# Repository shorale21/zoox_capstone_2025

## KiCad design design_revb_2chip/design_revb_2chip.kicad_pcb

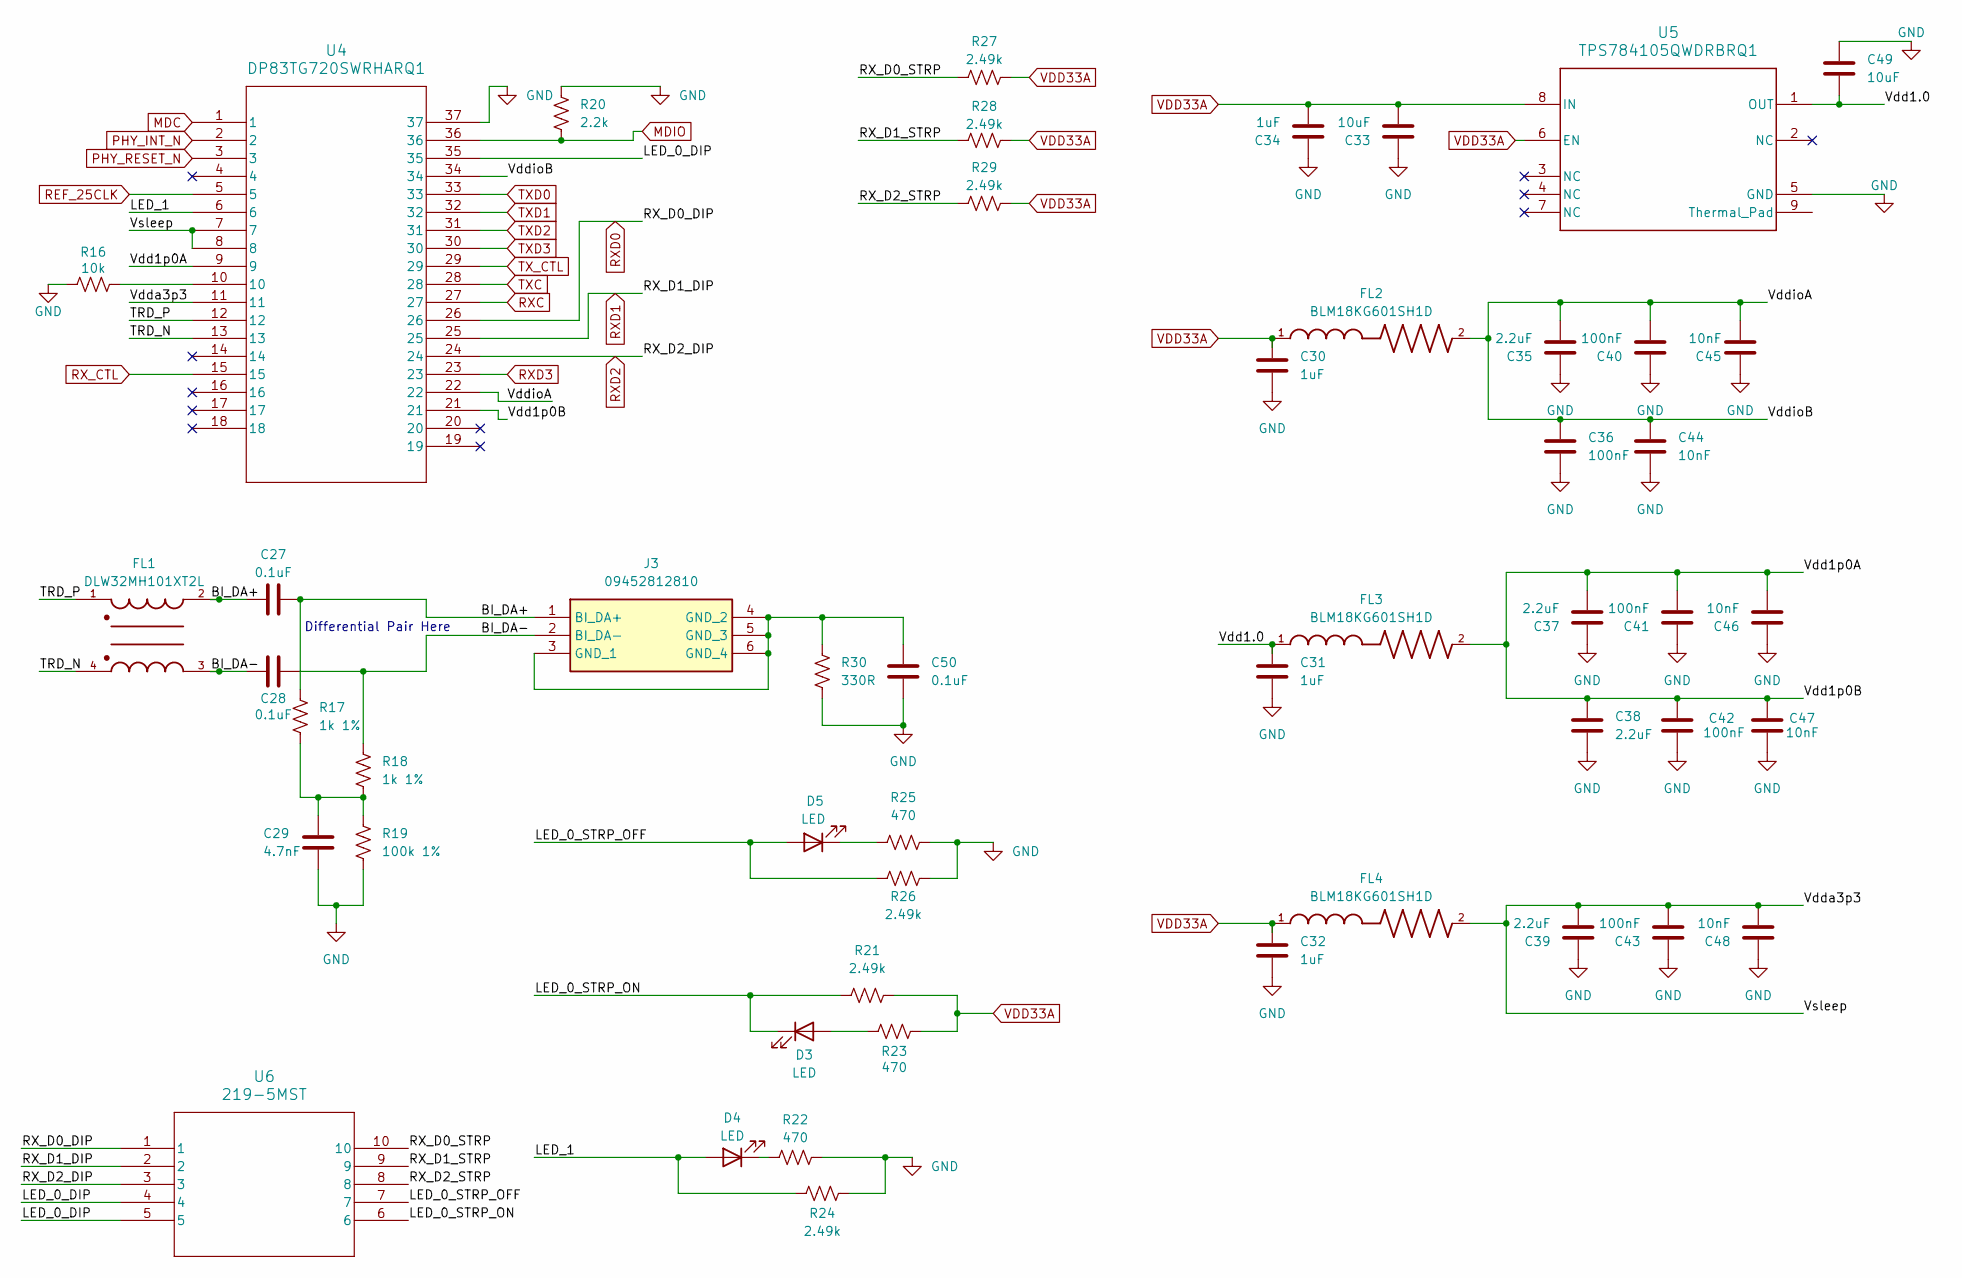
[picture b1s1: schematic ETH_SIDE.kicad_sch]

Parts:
C27, C28, C50: 0.1uF; C_0402_1005Metric
C29: 4.7nF; C_0603_1608Metric
C30, C32, C34: 1uF; C_0603_1608Metric
C31: 1uF; C_0402_1005Metric
C33: 10uF; C_0603_1608Metric
C35, C37, C38, C39: 2.2uF; C_0402_1005Metric
C36, C40, C41, C42, C43: 100nF; C_0402_1005Metric
C44, C46, C47, C48: 10nF; C_0402_1005Metric
C45: 10nF; C_0603_1608Metric
C49: 10uF; C_0402_1005Metric
D3, D4, D5: LED; LED_0603_1608Metric
FL1: DLW32MH101XT2L; FIL_DLW32MH101XT2L; PARTREV N/A
FL2, FL3, FL4: BLM18KG601SH1D; BEADC1608X95N
J3: 09452812810; hartingt1; Manufacturer_Part_Number 09452812810; Mouser Part Number 617-09452812810
R16: 10k; R_0805_2012Metric
R17, R18: 1k 1%; R_0805_2012Metric
R19: 100k 1%; R_0805_2012Metric
R20: 2.2k; R_0805_2012Metric
R21, R24, R26, R27, R28, R29: 2.49k; R_0805_2012Metric
R22, R23, R25: 470; R_0805_2012Metric
R30: 330R; R_0805_2012Metric
U4: DP83TG720SWRHARQ1; VQFN36_6X6_TEX
U5: TPS784105QWDRBRQ1; DRB0008J-IPC_A
U6: 219-5MST; SW5_219SMT

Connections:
/ETH_SIDE/BI_DA+: C27.1, C27.2, FL1.2, J3.1 (BI_DA+), R17.1
/ETH_SIDE/BI_DA-: C28.1, C28.2, FL1.3, J3.2 (BI_DA-), R18.1
/ETH_SIDE/LED_0_DIP: U4.35, U6.4, U6.5
/ETH_SIDE/LED_0_STRP_OFF: D5.2 (A), R26.1, U6.7
/ETH_SIDE/LED_0_STRP_ON: D3.1 (K), R21.1, U6.6
/ETH_SIDE/LED_1: D4.2 (A), R24.1, U4.6
/ETH_SIDE/RX_D0_STRP: R27.2, U6.10
/ETH_SIDE/RX_D1_STRP: R28.2, U6.9
/ETH_SIDE/RX_D2_STRP: R29.2, U6.8
/ETH_SIDE/TRD_N: FL1.4, U4.13
/ETH_SIDE/TRD_P: FL1.1, U4.12
/ETH_SIDE/Vdd1.0: C31.1, C49.2, FL3.1, U5.1 (OUT)
/ETH_SIDE/Vdd1p0A: C37.2, C38.1, C41.2, C42.1, C46.2, C47.1, FL3.2, U4.9, U4.21
/ETH_SIDE/Vdda3p3: C39.2, C43.2, C48.2, FL4.2, U4.7, U4.8, U4.11
/ETH_SIDE/VddioA: C35.2, C36.1, C40.2, C44.1, C45.2, FL2.2, U4.22, U4.34; also elsewhere on the board
GND: C29.2, C30.2, C31.2, C32.2, C33.1, C34.1, C35.1, C36.2, C37.1, C38.2, C39.1, C40.1, C41.1, C42.2, C43.1, C44.2, C45.1, C46.1, C47.2, C48.1, C49.1, C50.2, R16.2, R19.2, R20.1, R22.1, R24.2, R25.1, R26.2, R30.1, U4.37, U5.5 (GND); also elsewhere on the board
MDC: U4.1; also elsewhere on the board
MDIO: R20.2, U4.36; also elsewhere on the board
unnamed: C29.1, R17.2, R18.2, R19.1
unnamed: D3.2 (A), R23.1
unnamed: D4.1 (K), R22.2
unnamed: D5.1 (K), R25.2
unnamed: C50.1, J3.3 (GND_1), J3.4 (GND_2), J3.5 (GND_3), J3.6 (GND_4), R30.2
unnamed: R16.1, U4.10
PHY_INT_N: U4.2; also elsewhere on the board
PHY_RESET_N: U4.3; also elsewhere on the board
REF_25CLK: U4.5; also elsewhere on the board
RXC: U4.27; also elsewhere on the board
RXD0: U4.26, U6.1; also elsewhere on the board
RXD1: U4.25, U6.2; also elsewhere on the board
RXD2: U4.24, U6.3; also elsewhere on the board
RXD3: U4.23; also elsewhere on the board
RX_CTL: U4.15; also elsewhere on the board
TXC: U4.28; also elsewhere on the board
TXD0: U4.33; also elsewhere on the board
TXD1: U4.32; also elsewhere on the board
TXD2: U4.31; also elsewhere on the board
TXD3: U4.30; also elsewhere on the board
TX_CTL: U4.29; also elsewhere on the board
VDD33A: C30.1, C32.1, C33.2, C34.2, FL2.1, FL4.1, R21.2, R23.2, R27.1, R28.1, R29.1, U5.6 (EN), U5.8 (IN); also elsewhere on the board

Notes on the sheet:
Differential Pair Here

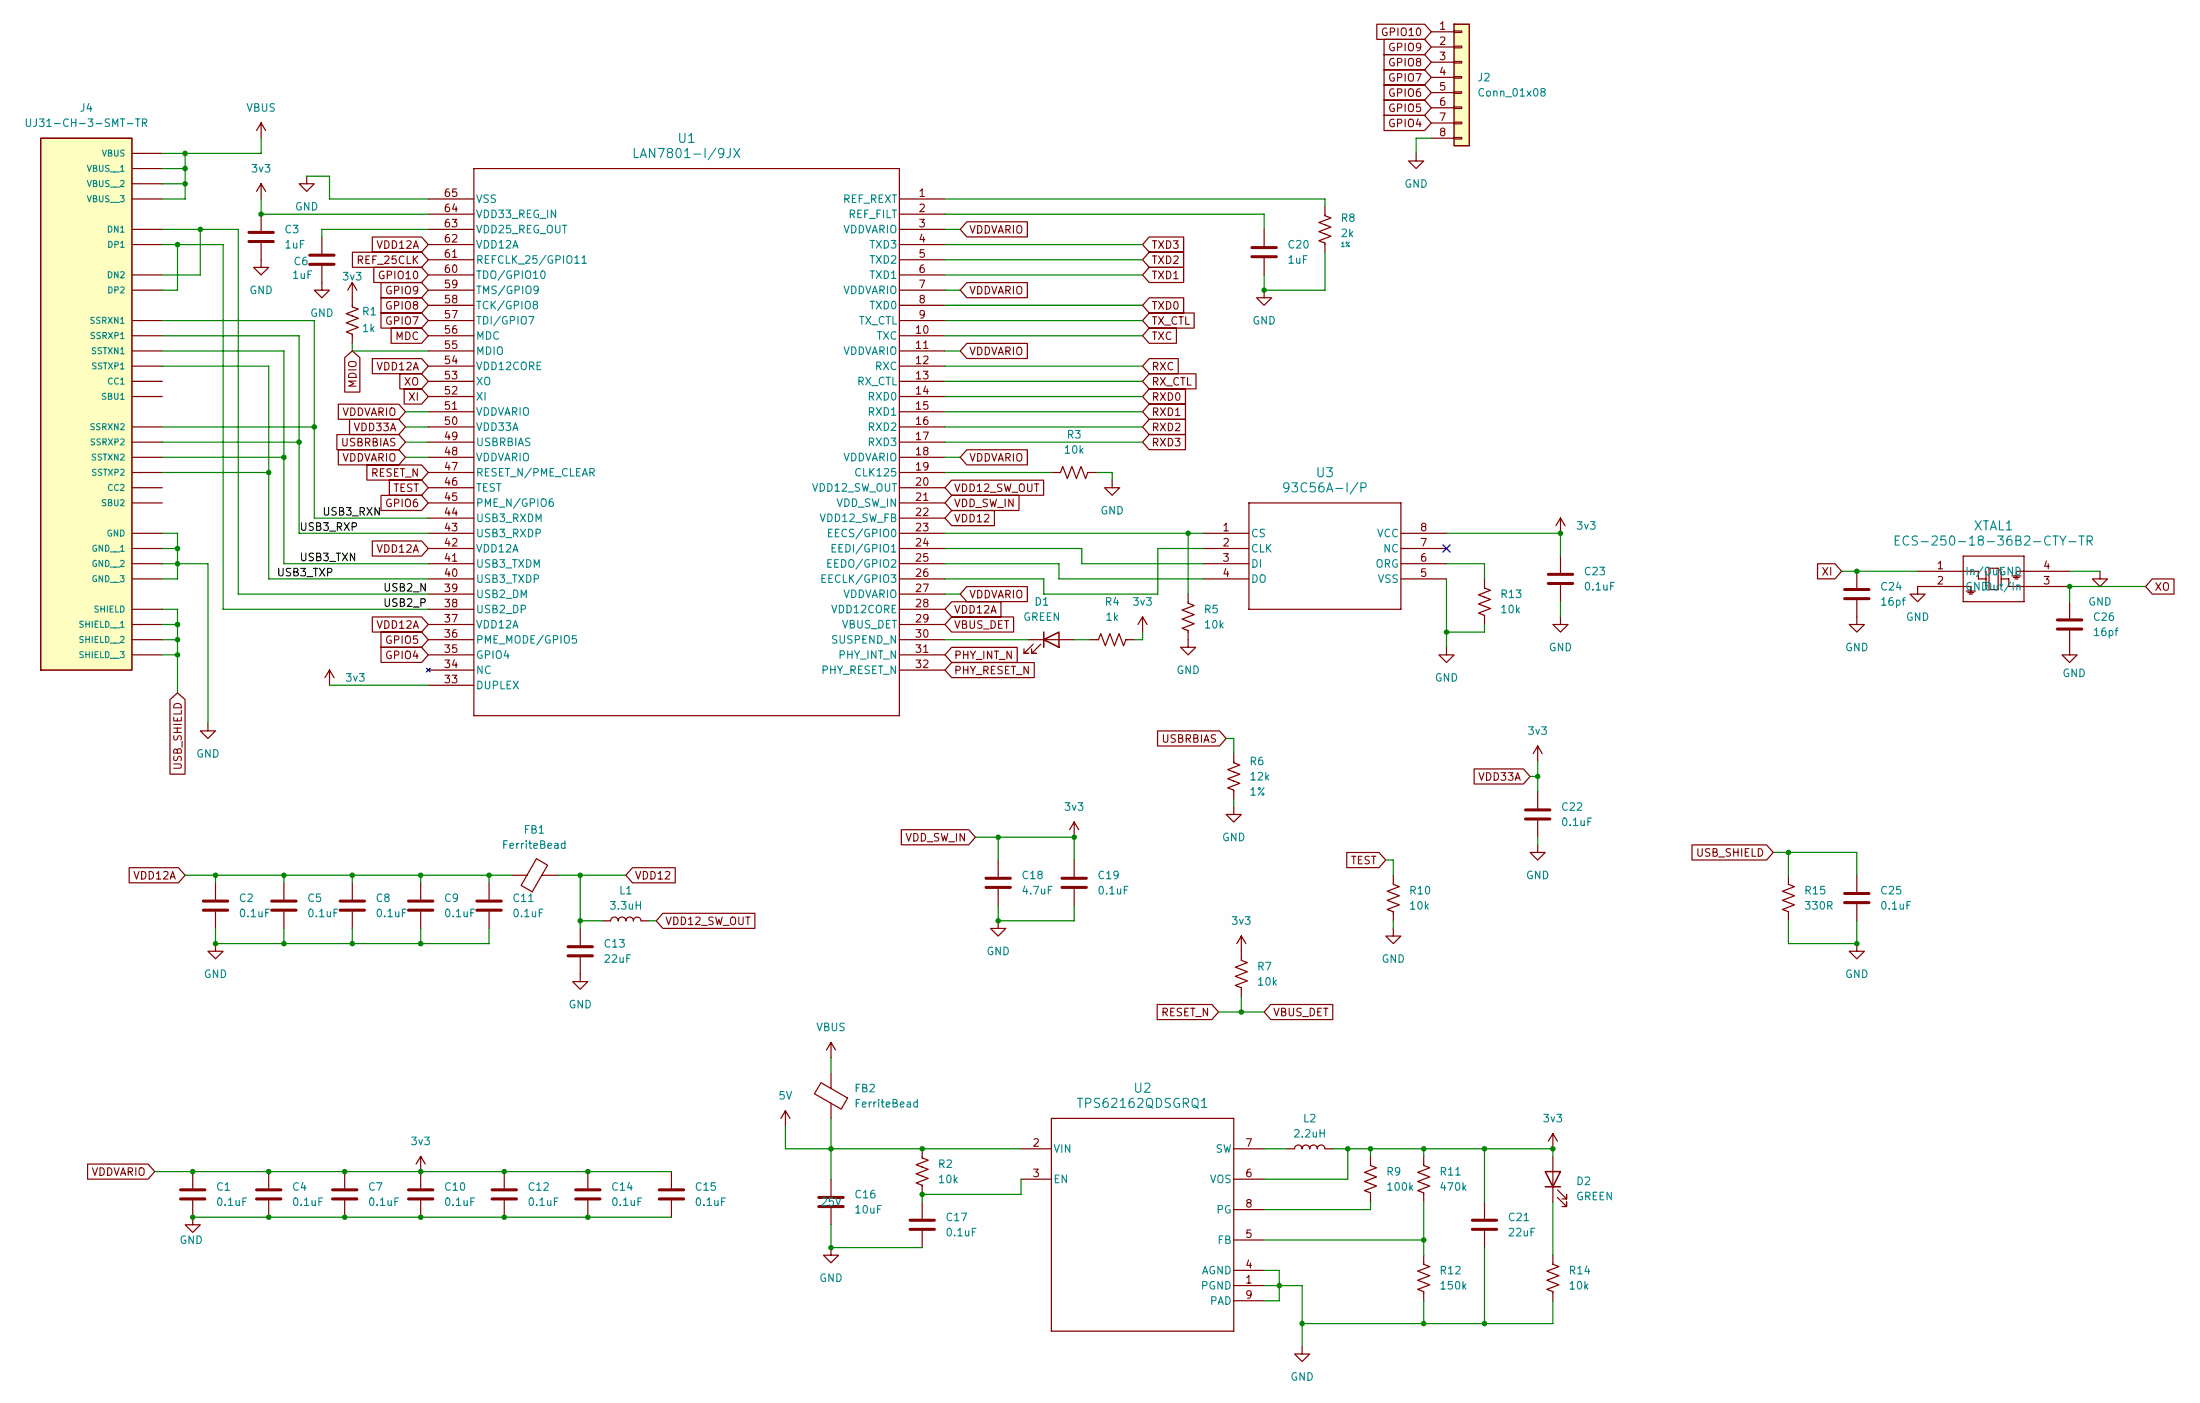
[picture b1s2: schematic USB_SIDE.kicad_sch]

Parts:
C1, C2, C4, C5, C7, C8, C9, C10, C11, C12, C14, C15, C17, C19, C22, C23, C25: 0.1uF; C_0402_1005Metric
C3: 1uF; C_0603_1608Metric
C6, C20: 1uF; C_0402_1005Metric
C13, C21: 22uF; C_0603_1608Metric
C16: 10uF; C_0603_1608Metric; voltage 25V
C18: 4.7uF; C_0603_1608Metric
C24, C26: 16pf; C_0402_1005Metric
D1, D2: GREEN; LED_0603_1608Metric
FB1, FB2: FerriteBead; BEADC1608X95N
J2: Conn_01x08; PinHeader_1x08_P2.00mm_Horizontal
J4: UJ31-CH-3-SMT-TR; CUI_UJ31-CH-3-SMT-TR
L1: 3.3uH; L_Wurth_WE-LQSH-3012
L2: 2.2uH; L_1008_2520Metric
R1, R4: 1k; R_0805_2012Metric
R2, R3, R5, R7, R10, R13, R14: 10k; R_0805_2012Metric
R6: 12k; R_0402_1005Metric; tolerance 1%
R8: 2k; R_0402_1005Metric; tolerance 1%
R9: 100k; R_0805_2012Metric
R11: 470k; R_0805_2012Metric
R12: 150k; R_0805_2012Metric
R15: 330R; R_0805_2012Metric
U1: LAN7801-I/9JX; SQFN64_9JX_MCH
U2: TPS62162QDSGRQ1; DSG0008A
U3: 93C56A-I/P; PDIP8_300MC_MCH
XTAL1: ECS-250-18-36B2-CTY-TR; ECX-2236B2_ECS

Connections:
5V: C16.1, FB2.1, R2.2, U2.2 (VIN)
/USB_SIDE/USB2_N: J4.A7 (DN1), J4.B7 (DN2), U1.39 (USB2_DM)
/USB_SIDE/USB2_P: J4.A6 (DP1), J4.B6 (DP2), U1.38 (USB2_DP)
/USB_SIDE/USB3_RXN: J4.A10 (SSRXN2), J4.B10 (SSRXN1), U1.44 (USB3_RXDM)
/USB_SIDE/USB3_RXP: J4.A11 (SSRXP2), J4.B11 (SSRXP1), U1.43 (USB3_RXDP)
/USB_SIDE/USB3_TXN: J4.A3 (SSTXN1), J4.B3 (SSTXN2), U1.41 (USB3_TXDM)
/USB_SIDE/USB3_TXP: J4.A2 (SSTXP1), J4.B2 (SSTXP2), U1.40 (USB3_TXDP)
GND: C1.2, C2.2, C3.2, C4.2, C5.2, C6.2, C7.2, C8.2, C9.2, C10.2, C11.2, C12.2, C13.2, C14.2, C15.2, C16.2, C17.2, C18.2, C19.2, C20.2, C21.2, C22.2, C23.2, C24.2, C25.2, C26.2, J2.8, J4.A1 (GND), J4.A12 (GND__1), J4.B1 (GND__2), J4.B12 (GND__3), R3.1, R5.1, R6.1, R8.1, R10.1, R12.1, R13.1, R14.1, R15.1, U1.65 (VSS), U2.1 (PGND), U2.4 (AGND), U2.9 (PAD), U2.V, U3.5 (VSS), XTAL1.2 (GND), XTAL1.4 (GND); also elsewhere on the board
GPIO4: J2.7, U1.35 (GPIO4)
GPIO5: J2.6, U1.36 (PME_MODE/GPIO5)
GPIO6: J2.5, U1.45 (PME_N/GPIO6)
GPIO7: J2.4, U1.57 (TDI/GPIO7)
GPIO8: J2.3, U1.58 (TCK/GPIO8)
GPIO9: J2.2, U1.59 (TMS/GPIO9)
GPIO10: J2.1, U1.60 (TDO/GPIO10)
MDC: U1.56 (MDC); also elsewhere on the board
MDIO: R1.1, U1.55 (MDIO); also elsewhere on the board
unnamed: D1.2 (A), R4.2
unnamed: D1.1 (K), U1.30 (SUSPEND_N)
unnamed: D2.1 (K), R14.2
unnamed: R3.2, U1.19 (CLK125)
unnamed: U1.26 (EECLK/GPIO3), U3.2 (CLK)
unnamed: R5.2, U1.23 (EECS/GPIO0), U3.1 (CS)
unnamed: U1.24 (EEDI/GPIO1), U3.3 (DI)
unnamed: U1.25 (EEDO/GPIO2), U3.4 (DO)
unnamed: C20.1, U1.2 (REF_FILT)
unnamed: R8.2, U1.1 (REF_REXT)
unnamed: C6.1, U1.63 (VDD25_REG_OUT)
unnamed: C17.1, R2.1, U2.3 (EN)
unnamed: R11.1, R12.2, U2.5 (FB)
unnamed: R9.1, U2.8 (PG)
unnamed: L2.1, U2.7 (SW)
unnamed: R13.2, U3.6 (ORG)
PHY_INT_N: U1.31 (PHY_INT_N); also elsewhere on the board
PHY_RESET_N: U1.32 (PHY_RESET_N); also elsewhere on the board
REF_25CLK: U1.61 (REFCLK_25/GPIO11); also elsewhere on the board
RESET_N: R7.1, U1.29 (VBUS_DET), U1.47 (RESET_N/PME_CLEAR)
RXC: U1.12 (RXC); also elsewhere on the board
RXD0: U1.14 (RXD0); also elsewhere on the board
RXD1: U1.15 (RXD1); also elsewhere on the board
RXD2: U1.16 (RXD2); also elsewhere on the board
RXD3: U1.17 (RXD3); also elsewhere on the board
RX_CTL: U1.13 (RX_CTL); also elsewhere on the board
TEST: R10.2, U1.46 (TEST)
TXC: U1.10 (TXC); also elsewhere on the board
TXD0: U1.8 (TXD0); also elsewhere on the board
TXD1: U1.6 (TXD1); also elsewhere on the board
TXD2: U1.5 (TXD2); also elsewhere on the board
TXD3: U1.4 (TXD3); also elsewhere on the board
TX_CTL: U1.9 (TX_CTL); also elsewhere on the board
USBRBIAS: R6.2, U1.49 (USBRBIAS)
USB_SHIELD: C25.1, J4.SH1 (SHIELD), J4.SH2 (SHIELD__1), J4.SH3 (SHIELD__2), J4.SH4 (SHIELD__3), R15.2
VBUS: FB2.2, J4.A4 (VBUS), J4.A9 (VBUS__1), J4.B4 (VBUS__2), J4.B9 (VBUS__3)
VDD12: C13.1, FB1.2, L1.1, U1.22 (VDD12_SW_FB)
VDD12A: C2.1, C5.1, C8.1, C9.1, C11.1, FB1.1, U1.28 (VDD12CORE), U1.37 (VDD12A), U1.42 (VDD12A), U1.54 (VDD12CORE), U1.62 (VDD12A)
VDD12_SW_OUT: L1.2, U1.20 (VDD12_SW_OUT)
VDD33A: C1.1, C3.1, C4.1, C7.1, C10.1, C12.1, C14.1, C15.1, C18.1, C19.1, C21.1, C22.1, C23.1, D2.2 (A), L2.2, R1.2, R4.1, R7.2, R9.2, R11.2, U1.3 (VDDVARIO), U1.7 (VDDVARIO), U1.11 (VDDVARIO), U1.18 (VDDVARIO), U1.21 (VDD_SW_IN), U1.27 (VDDVARIO), U1.33 (DUPLEX), U1.48 (VDDVARIO), U1.50 (VDD33A), U1.51 (VDDVARIO), U1.64 (VDD33_REG_IN), U2.6 (VOS), U3.8 (VCC); also elsewhere on the board
XI: C24.1, U1.52 (XI), XTAL1.1 (In/Out)
XO: C26.1, U1.53 (XO), XTAL1.3 (Out/In)

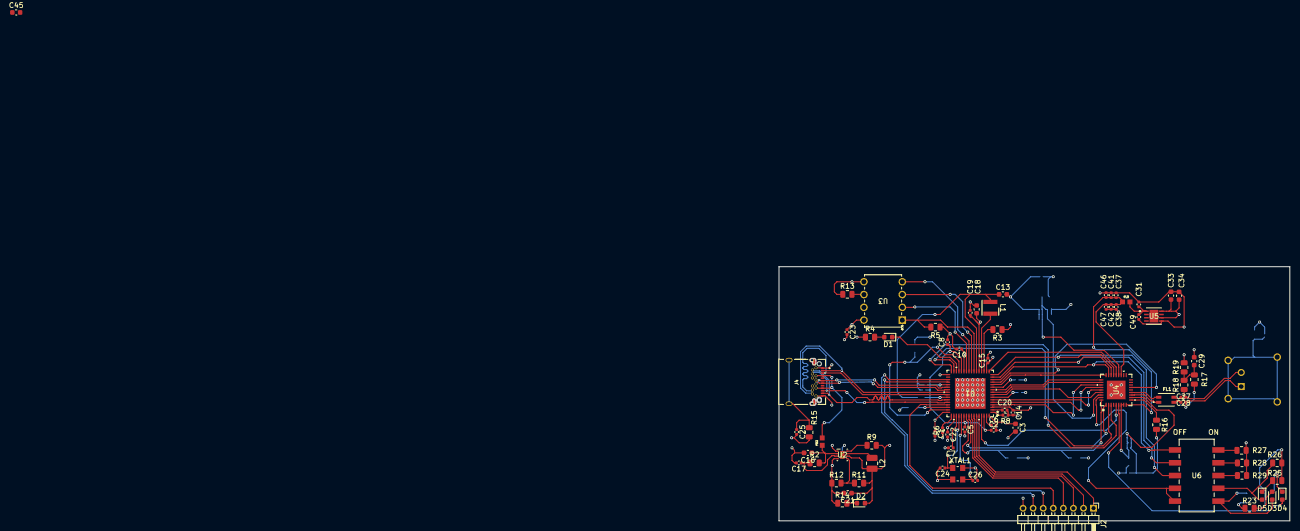
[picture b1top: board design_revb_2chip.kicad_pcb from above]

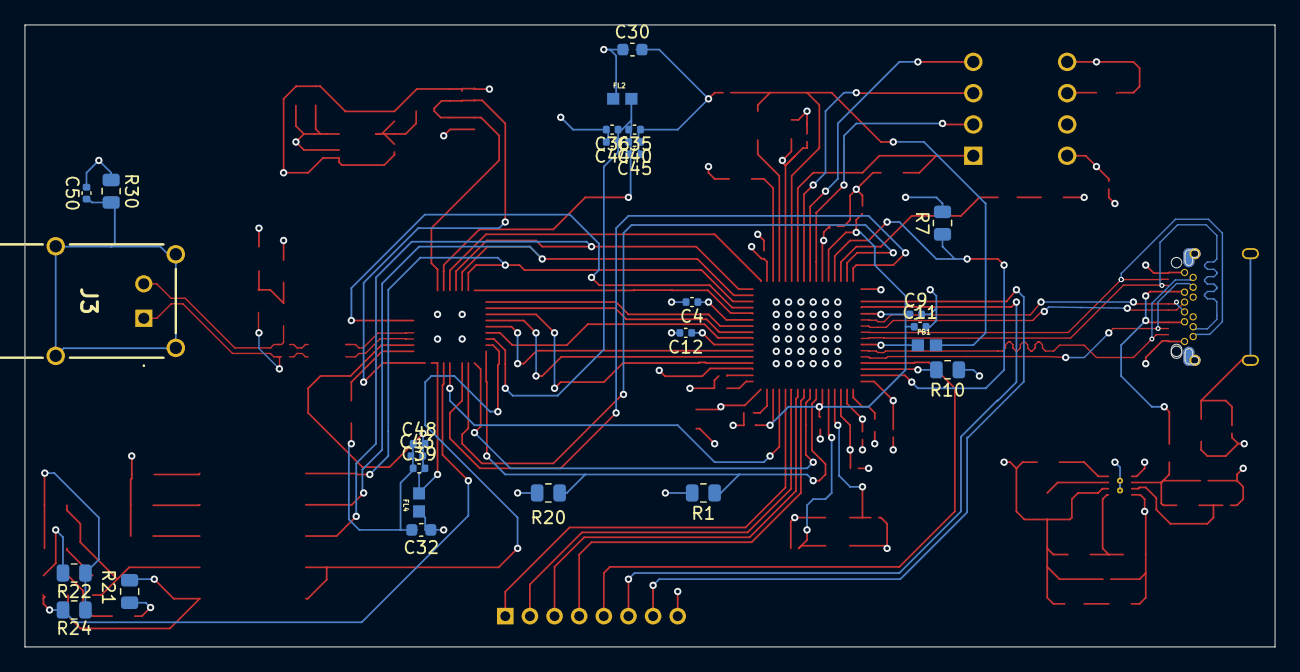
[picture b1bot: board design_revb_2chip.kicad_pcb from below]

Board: 4 copper layers, 101.5 x 50.5 mm, 104 parts (27 on the bottom side), 80 nets.

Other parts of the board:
C45#2: 10nF; C_0402_1005Metric

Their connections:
/ETH_SIDE/VddioA: C45#2.2; also elsewhere on the board
GND: C45#2.1; also elsewhere on the board

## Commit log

2025-01-10 Initial Push
    Pushed the empty KiCAD project
2025-01-12 Symbols & Footprints
    - Created Symbol and Footprint Libraries
    - Added chips and footprints to libraries
2025-01-13 Initial Schematic Sheets
    Created Initial Schematic Sheets and placed initial symbols for editing.
2025-01-13 Harting Symbol
    added harting symbol library
2025-01-13 Quick Fix & Harting Symbol
2025-01-15 USB Side Progress 1
    - EEPROM done
    - data components done
    - some power components done
2025-01-16 Roughly Finishes
    First Draft of Completed USB-Side Schematic
    - LAN7801 connections
    - Regulator
    - Oscillator
2025-01-17 finished initial schematic
2025-01-17 ready to merge
2025-01-17 Small Fixes
    Modifying both pages to try and resolve differences in pins
2025-01-17 Pin Renames
2025-01-22 Annotation
    Quick Annotation Update before PCB
2025-01-22 ground orientation + resistor tolerances
2025-01-23 Preliminary Footprint Assignments
    - initial footprint assignments
2025-01-23 PCB Created
    Footprints all placed in the PCB document
2025-01-24 Some PCB Design
    - USB side PCB design (mostly done)
2025-01-24 updated schm
2025-01-24 More PCB 2
    - USB side PCB Update
2025-01-24 USB Side PCB Update
    - small update to the PCB on the USB side
2025-01-24 added dip switch block
2025-01-25 PCB Update
2025-01-26 USB_Side Prelim Completion
    - finished USB side with no revisions
2025-01-27 routing eth side
2025-01-27 routing doen
2025-01-27 Semi-Final Fixes
2025-01-28 PCB fixes
2025-01-29 Final PCB Fixes
2025-01-29 PCB Fixes/Completion
2025-01-31 Minor routing fixes + component resizing
2025-01-31 footprint resizing
2025-02-10 Final Push for Rev A 1.0
2025-03-06 Reorganization
    Allow for future versions of rev b
